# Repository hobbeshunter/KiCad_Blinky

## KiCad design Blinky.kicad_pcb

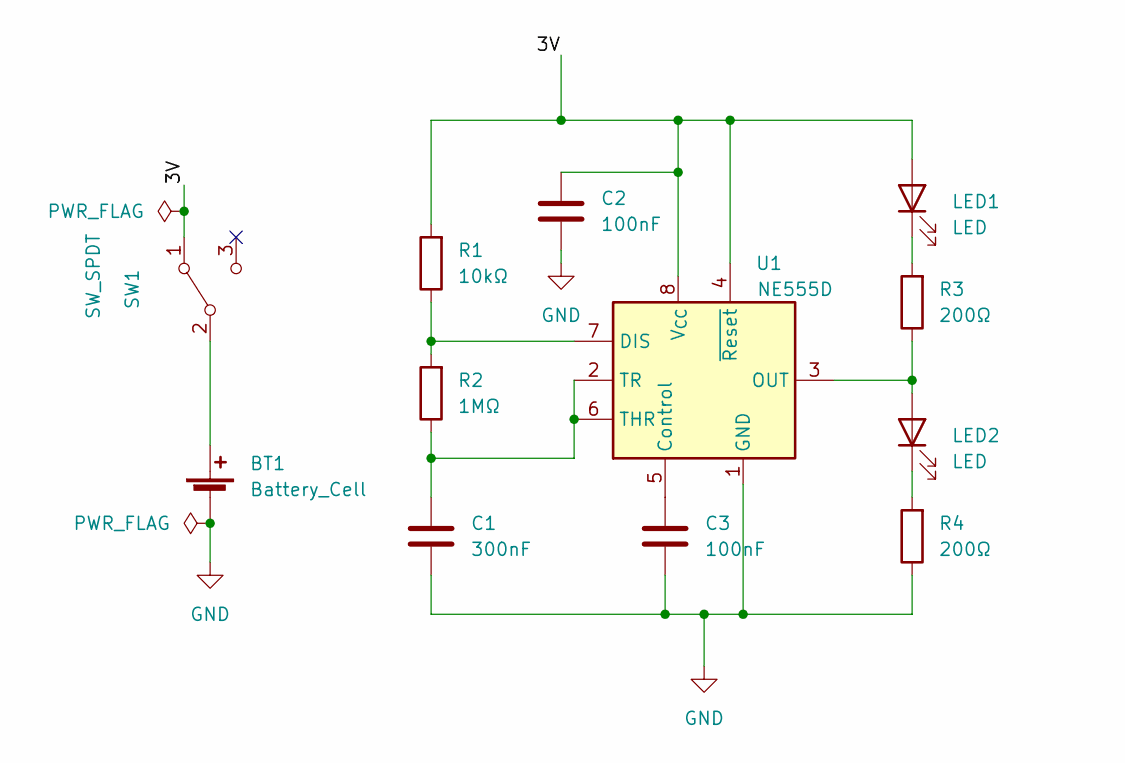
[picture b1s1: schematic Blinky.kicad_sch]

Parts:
BT1: Battery_Cell; BatteryHolder_Keystone_3000_1x12mm
C1: 300nF; C_0805_2012Metric_Pad1.18x1.45mm_HandSolder
C2, C3: 100nF; C_0805_2012Metric_Pad1.18x1.45mm_HandSolder
LED1, LED2: LED; LED_0805_2012Metric_Pad1.15x1.40mm_HandSolder
R1: 10kΩ; R_0805_2012Metric_Pad1.20x1.40mm_HandSolder
R2: 1MΩ; R_0805_2012Metric_Pad1.20x1.40mm_HandSolder
R3, R4: 200Ω; R_0805_2012Metric_Pad1.20x1.40mm_HandSolder
SW1: SW_SPDT; SW_SPDT_PCM12
U1: NE555D; SOIC-8_3.9x4.9mm_P1.27mm

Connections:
/3V: C2.1, LED1.2 (A), R1.2, SW1.1 (A), U1.4 (~Reset), U1.8 (V_{CC})
GND: BT1.2 (-), C1.2, C2.2, C3.2, R4.1, U1.1 (GND)
unnamed: BT1.1 (+), SW1.2 (B)
unnamed: C1.1, R2.1, U1.2 (TR), U1.6 (THR)
unnamed: C3.1, U1.5 (Control)
unnamed: LED1.1 (K), R3.2
unnamed: LED2.1 (K), R4.2
unnamed: LED2.2 (A), R3.1, U1.3 (OUT)
unnamed: R1.1, R2.2, U1.7 (DIS)

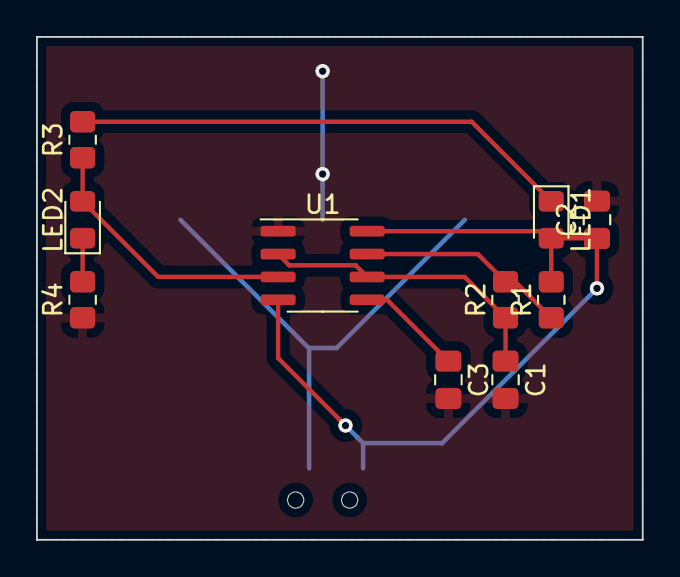
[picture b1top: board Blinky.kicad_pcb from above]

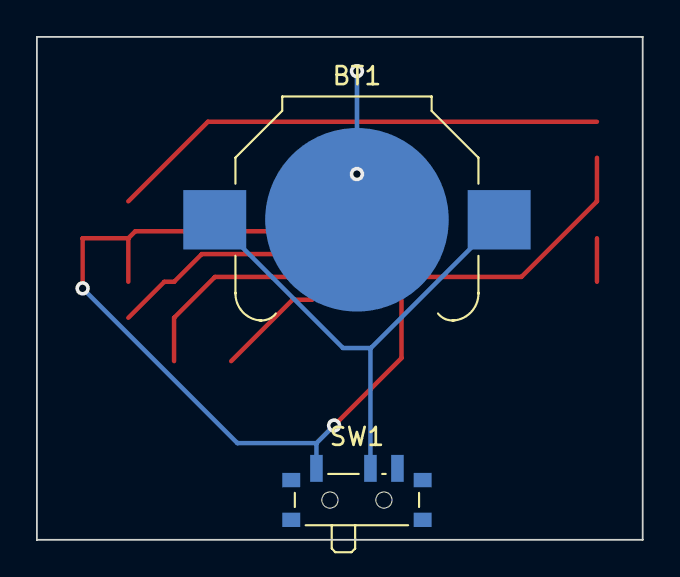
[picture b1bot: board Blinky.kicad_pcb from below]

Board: 2 copper layers, 33.7 x 27.9 mm, 12 parts (2 on the bottom side), 9 nets.
